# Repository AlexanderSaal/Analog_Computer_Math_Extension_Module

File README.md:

# Analog Computer: Math Extension Module

This repository provides a math extension module for analog computing applications. The module provides two absolute value functions, two square-root functions, and one logarithmic value function (base $10$ and $e$) of the input. Each output features an indicator LED that provides visual feedback proportional to the output value.

## Module Schematic

**<ins>Absolute function(x):</ins>** $x \rightarrow |x|$

The circuit for the absolute value function incorporates two different designs.

The left circuit is based on individual diodes and represents the classical implementation of an absolute value circuit. This circuit follows the design outlined in the document [PRECISION ABSOLUTE VALUE CIRCUITS](https://www.ti.com/lit/pdf/sboa068) from BURR-BROWN/TI.

The right circuit is similar but with one important difference: the diodes are replaced with P-channel MOSFETs on a single substrate. This should ensure thermal coupling and closely specifications of the two MOSFETs.

**<ins>Square-Root function(x):</ins>** $x \rightarrow \sqrt{x}$

The circuit implementation of the square-root function is based on the feedback principle. A multiplier squares the output signal and feeds it back into an open-loop amplifier to yield the inverse function. The diode in the feedback path ensures that only negative values are allowed at the input; otherwise, the output remains close to zero, preventing overload. For ease of use, an inverter is placed before the input, resulting in the overall transfer function of the module:

$$
\begin{align}
  f(x) = \begin{cases}
  \sqrt{x} & \text{if } x > 0 \\
  0 & \text{if } x \le 0
  \end{cases}
\end{align}
$$

This circuit design is based on the schematic and principals presented in the book [Analog and Hybrid Computer Programming](https://www.degruyter.com/document/doi/10.1515/9783110662207/html) by Prof. Dr. Bernd Ulmann and the [book on the THAT Analog Computer](http://www.astro-electronic.de/THAT_Analog_Computer_Book.pdf) by Michael Koch.

**<ins>Logarithmic function(x):</ins>** $x \rightarrow \mathrm{log}_{10}(x)$ and $x \rightarrow \mathrm{log}_{e}(x)$

The logarithm function circuit is based on the [LOG200](https://www.ti.com/product/LOG200) chip from Texas Instruments. The input voltage must be scaled down from $\pm 10 \, V$ to the chip's maximum accepted range of $\pm 5 \, V$. According to the datasheet, $-5V$ falls within the absolute maximum ratings and will not damage the chip.

The transfer function of the LOG200 chip is

$$ V_\mathrm{LOG} = 250 \, mV \cdot \mathrm{log}_{10} \left( \frac{I_1}{I_2} \right) $$

which depends on the ratio of the input currents $I_1$ and $I_2$. The input current $I_2$ is wired to the internal $1 \, \mu A$ precision current source. Accordingly, the input voltage has to be scaled using a precision (0.05\%) $50k\Omega$ resistor to give the appropriate current $I_1$. Since we want to map the output to the full range of our machine unit, $\pm1$ or $\pm 10 \,V$, a "20x" amplifier is placed after the output of the Voltage $V_\mathrm{LOG}$.

With this scaling, the following input-output relationship is achieved:

| Input      | Current $I_1$ | Output of LOG200 | Circuit Output |
|------------|---------------|------------------|----------------|
|$0.001 \, V$|$0.01 \, \mu A$|$-0.5\,V$         | $-10 \, V$     |
|$0.01 \, V$ |$0.1 \, \mu A$ |$-0.25\,V$        | $-5 \, V$      |
|$0.1 \, V$  |$1 \, \mu A$   |$0\,V$            | $0 \, V$       |
|$1 \, V$    |$10 \, \mu A$  |$0.25\,V$         | $5 \, V$       |
|$10 \, V$   |$100 \, \mu A$ |$0.5\,V$          | $10 \, V$      |

To additionally compute the natural logarithm $\mathrm{log}_e$, we use the relation:

$$ \mathrm{log}_{e}(x) = \frac{\mathrm{log}_{10}(x)}{\mathrm{log}_{10}(e)} = 2.303 \cdot \mathrm{log}_{10}(x) $$

A simple scaling amplifier with a gain of $0.2303x$ is used to provide the output of $\mathrm{log}_e(x) / 10$.

This circuit design and Input/Output scaling are based on the circuit presented in the book [Analog and Hybrid Computer Programming](https://www.degruyter.com/document/doi/10.1515/9783110662207/html) by Prof. Dr. Bernd Ulmann. I took the liberty of replacing the LOG112 with the LOG200 chip and adding the natural logarithm functionality.

## BOM

**<ins>Main Module:</ins>** 

|Reference                                   |Value              |Footprint                          |QUANTITY|
|--------------------------------------------|-------------------|-----------------------------------|--------|
|C1,C2,C14,C17                               |10u                |1206 / 3216Metric                  |4       |
|C3,C5                                       |0.33u              |1206 / 3216Metric                  |2       |
|C4,C6,C9,C10,C15,C16,C19,C20,C22-C25,C27,C28|1u                 |1206 / 3216Metric                  |14      |
|C7,C8                                       |10p                |1206 / 3216Metric                  |2       |
|C11,C12                                     |33p                |1206 / 3216Metric                  |2       |
|C13,C18                                     |1n                 |1206 / 3216Metric                  |2       |
|C21,C26                                     |68p                |1206 / 3216Metric                  |2       |
|D1                                          |12V_GREEN          |1206 / 3216Metric                  |1       |
|D2                                          |-12V_RED           |1206 / 3216Metric                  |1       |
|D3-D6                                       |BAT43W-V           |1206 / 3216Metric                  |4       |
|IC1,IC2                                     |AD633              |SOIC-8                             |2       |
|J1                                          |Conn_01x23_Pin     |PinHeader_1x23_P2.54mm_Vertical    |1       |
|J2                                          |Conn_02x05_Odd_Even|PinHeader_2x05_P2.54mm_Vertical    |1       |
|Q1                                          |PMV250EPEA         |SOT-23                             |1       |
|Q2                                          |PMV450ENEA         |SOT-23                             |1       |
|R1                                          |11k2               |1206 / 3216Metric                  |1       |
|R2                                          |5k6                |1206 / 3216Metric                  |1       |
|R3-R8,R14                                   |100k               |1206 / 3216Metric                  |7       |
|R9                                          |50k (0.05p)        |1206 / 3216Metric                  |1       |
|R10,R11                                     |1M (0.05p)         |1206 / 3216Metric                  |2       |
|R12,R29-R32                                 |3k9                |1206 / 3216Metric                  |5       |
|R13                                         |1M5                |1206 / 3216Metric                  |1       |
|R15                                         |4.26k              |1206 / 3216Metric                  |1       |
|R16                                         |400k               |1206 / 3216Metric                  |1       |
|R17,R18,R22-R24,R28                         |100k (0.1p)        |1206 / 3216Metric                  |6       |
|R19,R20,R25,R26                             |1M (0.1p)          |1206 / 3216Metric                  |4       |
|R21,R27                                     |25k (0.1p)         |1206 / 3216Metric                  |2       |
|RV1                                         |100k               |Potentiometer_Bourns_3296W_Vertical|1       |
|RV2                                         |2k                 |Potentiometer_Bourns_3296W_Vertical|1       |
|U1                                          |MC7805ACTG         |TO-220-3_Vertical                  |1       |
|U2                                          |MC7905BTG          |TO-220-3_Vertical                  |1       |
|U3,U4                                       |VCAN16A2           |VCAN16A2-03S-E3-08                 |2       |
|U5                                          |SI3993CDV-T1-GE3   |TSOT-23-6                          |1       |
|U6,U8-U10                                   |TLE2074IDWR        |SOIC-14\_3.9x8.7mm\_P1.27mm        |4       |
|U7                                          |LOG200             |VQFN-16                            |1       |

**<ins>Middleplate:</ins>**

|Reference                                   |Value              |Footprint                          |QUANTITY|
|--------------------------------------------|-------------------|-----------------------------------|--------|
|D1-D5                                       |BI color LED       |LED_D3.0mm_FlatTop                 |5       |
|J1                                          |Conn_01x23_Pin     |PinSocket_1x23_P2.54mm_Vertical    |1       |
|U1-U6                                       |VCAN16A2           |VCAN16A2-03S-E3-08                 |6       |

## List of special Components:

- OP-amp: [TLE2074IDWR](https://www.digikey.de/en/products/detail/texas-instruments/TLE2074IDWR/2799317) (Upgrade of the [TL074HIDR](https://www.digikey.de/en/products/detail/texas-instruments/TL074HIDR/13563033))
- logarithmic amplifier: [TL441CN](https://www.digikey.de/de/products/detail/texas-instruments/TL441CN/1675117), [LOG112AID](https://www.digikey.de/de/products/detail/texas-instruments/LOG112AID/486371), [LOG200RGTT](https://www.digikey.de/de/products/detail/texas-instruments/LOG200RGTT/25821029), [LOG200-datasheet](https://www.ti.com/product/LOG200)
- Multiplier: [AD633JRZ](https://www.digikey.de/en/products/detail/analog-devices-inc/AD633JRZ/617831) to [AD835ARZ](https://www.digikey.de/en/products/detail/analog-devices-inc/AD835ARZ-REEL7/621103)
- P-MOSFET: [SSFQ3805](https://www.digikey.de/en/products/detail/good-ark-semiconductor/SSFQ3805/18667583), [SI3993CDV-T1-GE3](https://www.digikey.de/en/products/detail/vishay-siliconix/SI3993CDV-T1-GE3/4876436)
- P-MOSFET (matched pair):[ALD1117SAL](https://www.digikey.de/en/products/detail/advanced-linear-devices-inc/ALD1117SAL/2414325)
- 16-BIT Schottky Barrier Diode Bus-Termination Array: [SN74S1053PWR](https://www.digikey.de/en/products/detail/texas-instruments/SN74S1053PWR/509741)
- 2 PNP (Dual) Matched Pair:[site](https://www.diodes.com/products/discrete-semiconductors/bipolar-transistors/transistor-bjt-master-table/matchedpair/#), [DMMT3906W-7-F](https://www.digikey.de/en/products/detail/diodes-incorporated/DMMT3906W-7-F/717760), [BCM847BS](https://www.digikey.de/en/products/detail/diotec-semiconductor/BCM847BS/22600802)
- +5V Regulator: [MC7805ACTG](https://www.digikey.de/en/products/detail/onsemi/MC7805ACTG/1481210), [MC7805ABTG](https://www.digikey.de/en/products/detail/onsemi/MC7805ABTG/921035)
- -5V Regulator: [MC7905BTG](https://www.digikey.de/en/products/detail/onsemi/MC7905BTG/1481513)

## License

This work is published under the [CERN Open Hardware Licence Version 2 - Strongly Reciprocal](LICENSE)

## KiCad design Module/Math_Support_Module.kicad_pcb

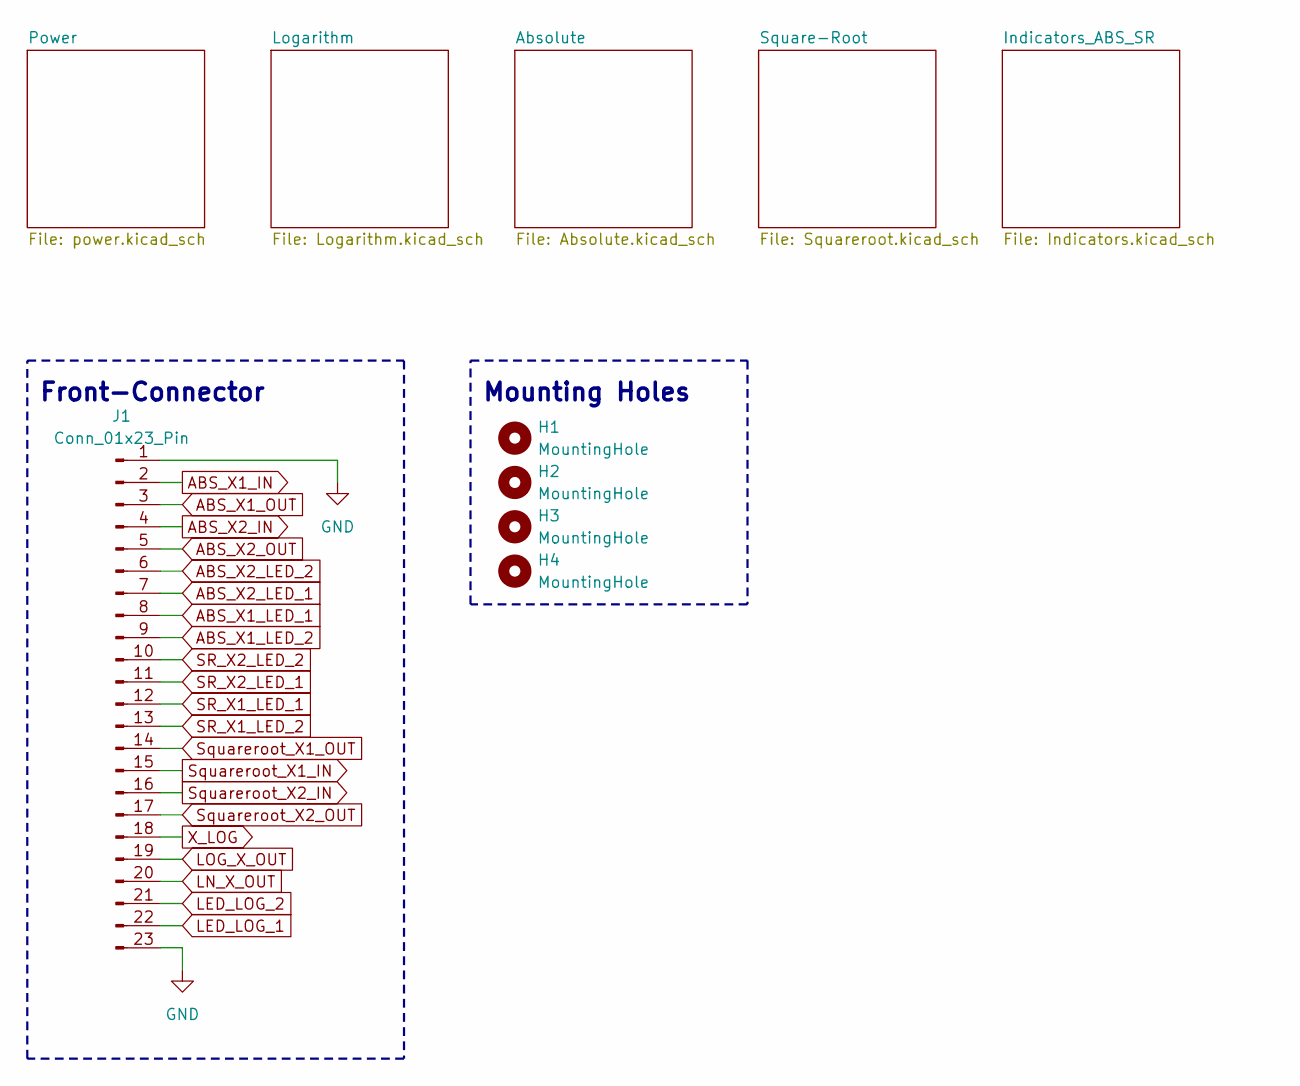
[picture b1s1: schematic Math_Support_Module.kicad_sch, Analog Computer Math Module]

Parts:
H1, H2, H3, H4: MountingHole; MountingHole_3.2mm_M3_DIN965
J1: Conn_01x23_Pin; PinHeader_1x23_P2.54mm_Vertical

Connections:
ABS_X1_IN: J1.2; also elsewhere on the board
ABS_X1_LED_1: J1.8; also elsewhere on the board
ABS_X1_LED_2: J1.9; also elsewhere on the board
ABS_X1_OUT: J1.3; also elsewhere on the board
ABS_X2_IN: J1.4; also elsewhere on the board
ABS_X2_LED_1: J1.7; also elsewhere on the board
ABS_X2_LED_2: J1.6; also elsewhere on the board
ABS_X2_OUT: J1.5; also elsewhere on the board
GND: J1.1, J1.23; also elsewhere on the board
LED_LOG_1: J1.22; also elsewhere on the board
LED_LOG_2: J1.21; also elsewhere on the board
LN_X_OUT: J1.20; also elsewhere on the board
LOG_X_OUT: J1.19; also elsewhere on the board
SR_X1_LED_1: J1.12; also elsewhere on the board
SR_X1_LED_2: J1.13; also elsewhere on the board
SR_X2_LED_1: J1.11; also elsewhere on the board
SR_X2_LED_2: J1.10; also elsewhere on the board
Squareroot_X1_IN: J1.15; also elsewhere on the board
Squareroot_X1_OUT: J1.14; also elsewhere on the board
Squareroot_X2_IN: J1.16; also elsewhere on the board
Squareroot_X2_OUT: J1.17; also elsewhere on the board
X_LOG: J1.18; also elsewhere on the board

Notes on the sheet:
Mounting Holes
Front-Connector

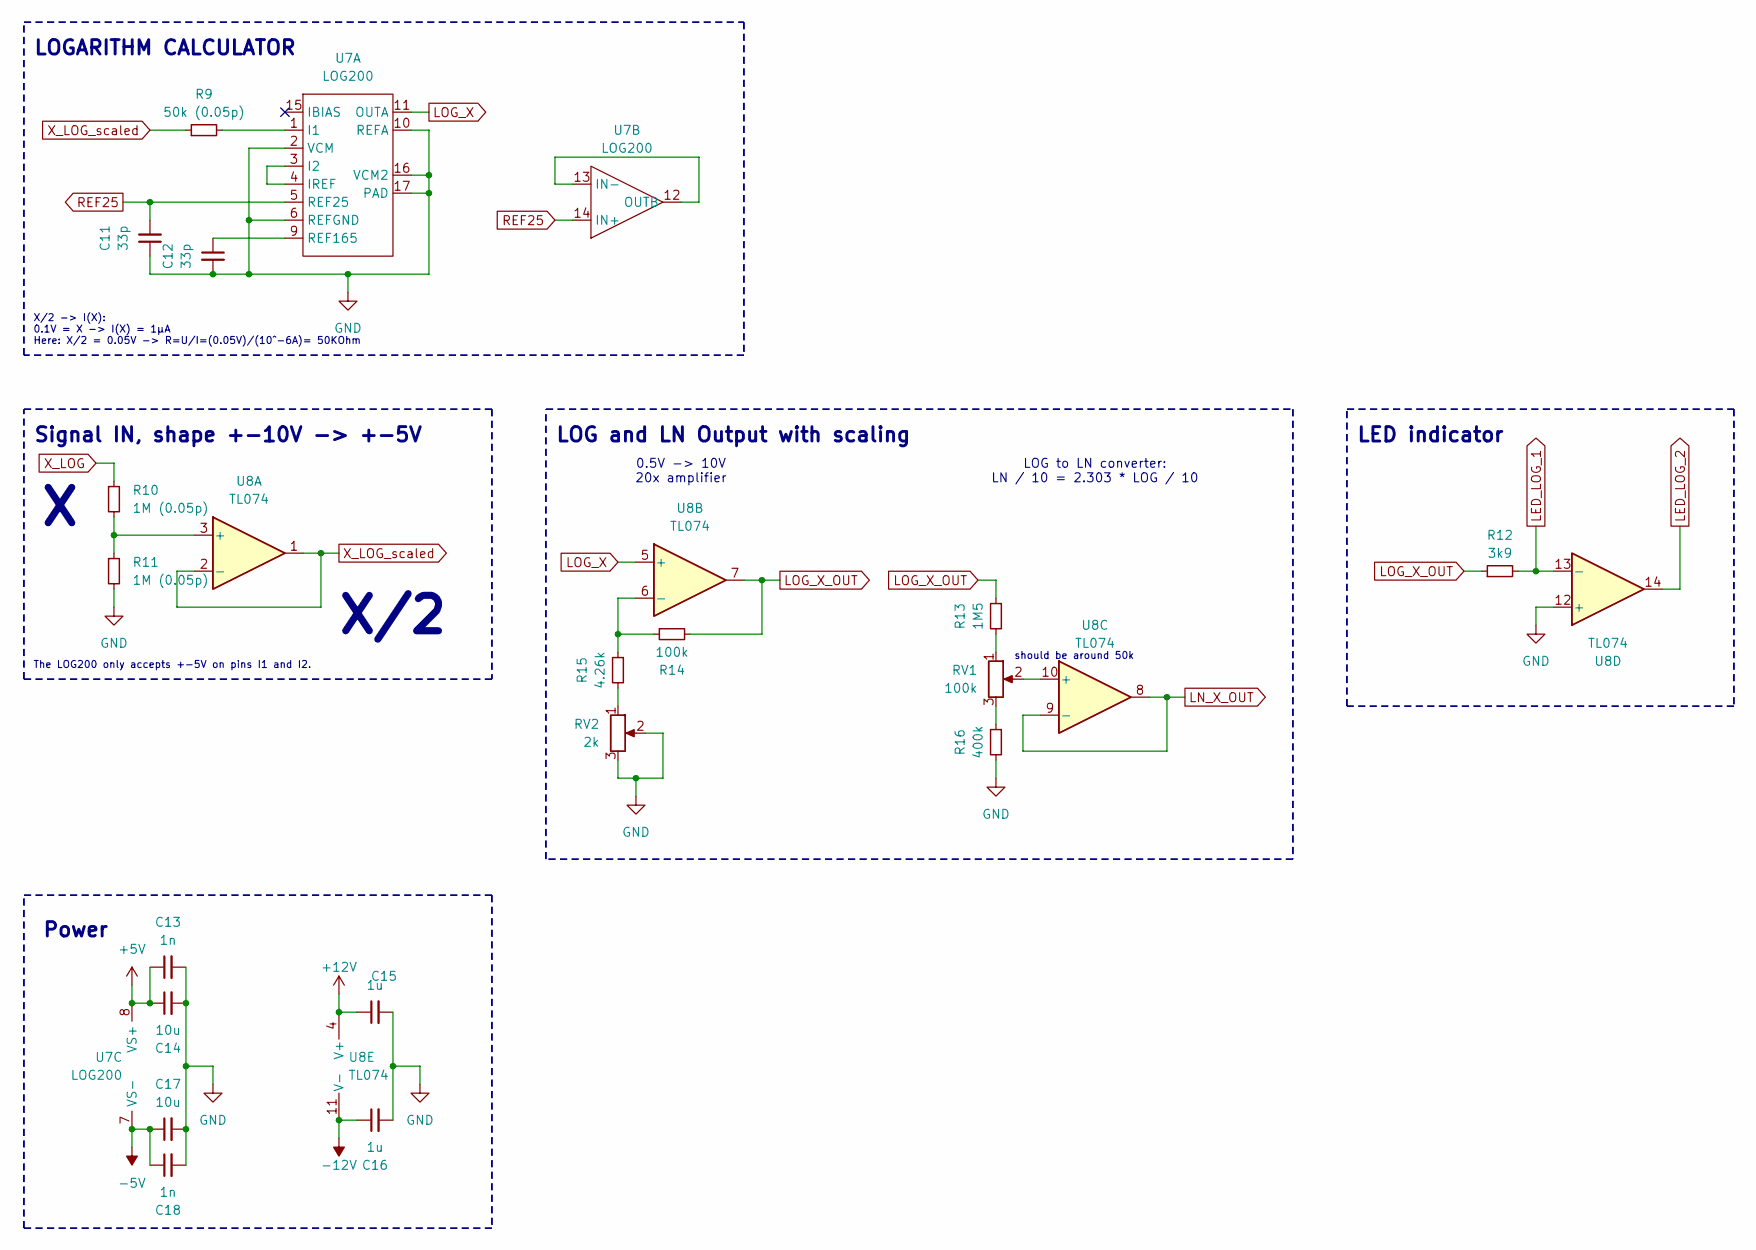
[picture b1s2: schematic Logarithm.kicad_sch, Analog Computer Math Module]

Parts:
C11, C12: 33p; C_1206_3216Metric_Pad1.33x1.80mm_HandSolder
C13, C18: 1n; C_1206_3216Metric_Pad1.33x1.80mm_HandSolder
C14, C17: 10u; C_1206_3216Metric_Pad1.33x1.80mm_HandSolder
C15, C16: 1u; C_1206_3216Metric_Pad1.33x1.80mm_HandSolder
R9: 50k (0.05p); R_1206_3216Metric_Pad1.30x1.75mm_HandSolder
R10, R11: 1M (0.05p); R_1206_3216Metric_Pad1.30x1.75mm_HandSolder
R12: 3k9; R_1206_3216Metric_Pad1.30x1.75mm_HandSolder
R13: 1M5; R_1206_3216Metric_Pad1.30x1.75mm_HandSolder
R14: 100k; R_1206_3216Metric_Pad1.30x1.75mm_HandSolder
R15: 4.26k; R_1206_3216Metric_Pad1.30x1.75mm_HandSolder
R16: 400k; R_1206_3216Metric_Pad1.30x1.75mm_HandSolder
RV1: 100k; Potentiometer_Bourns_3296W_Vertical
RV2: 2k; Potentiometer_Bourns_3296W_Vertical
U7: LOG200; VQFN-16-1EP_3x3mm_P0.5mm_EP1.6x1.6mm_ThermalVias
U8: TL074; SOIC-14_3.9x8.7mm_P1.27mm

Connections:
+5V: C13.1, C14.1, U7.8 (VS+); also elsewhere on the board
+12V: C15.1, U8.4 (V+); also elsewhere on the board
-5V: C17.1, C18.1, U7.7 (VS-); also elsewhere on the board
-12V: C16.1, U8.11 (V-); also elsewhere on the board
GND: C11.1, C12.2, C13.2, C14.2, C15.2, C16.2, C17.2, C18.2, R11.2, R16.2, RV2.2, RV2.3, U7.2 (VCM), U7.6 (REFGND), U7.10 (REFA), U7.16 (VCM2), U7.17 (PAD), U8.12 (+); also elsewhere on the board
LED_LOG_1: R12.2, U8.13 (-); also elsewhere on the board
LED_LOG_2: U8.14; also elsewhere on the board
LN_X_OUT: U8.8, U8.9 (-); also elsewhere on the board
LOG_X: U7.11 (OUTA), U8.5 (+)
LOG_X_OUT: R12.1, R13.1, R14.2, U8.7; also elsewhere on the board
unnamed: R13.2, RV1.1
unnamed: R15.2, RV2.1
unnamed: R16.1, RV1.3
unnamed: R9.2, U7.1 (I1)
unnamed: U7.3 (I2), U7.4 (IREF)
unnamed: C12.1, U7.9 (REF165)
unnamed: U7.12 (OUTB), U7.13 (IN-)
unnamed: R10.2, R11.1, U8.3 (+)
unnamed: R14.1, R15.1, U8.6 (-)
unnamed: RV1.2, U8.10 (+)
REF25: C11.2, U7.5 (REF25), U7.14 (IN+)
X_LOG: R10.1; also elsewhere on the board
X_LOG_scaled: R9.1, U8.1, U8.2 (-)

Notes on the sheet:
Power
X/2 -> I(X): 0.1V = X -> I(X) = 1µA Here: X/2 = 0.05V -> R=U/I=(0.05V)/(10^-6A)= 50KOhm
LED indicator
Signal IN, shape +-10V -> +-5V
LOG to LN converter: LN / 10 = 2.303 * LOG / 10
The LOG200 only accepts +-5V on pins I1 and I2.
X/2
0.5V -> 10V 20x amplifier
should be around 50k
LOGARITHM CALCULATOR
LOG and LN Output with scaling

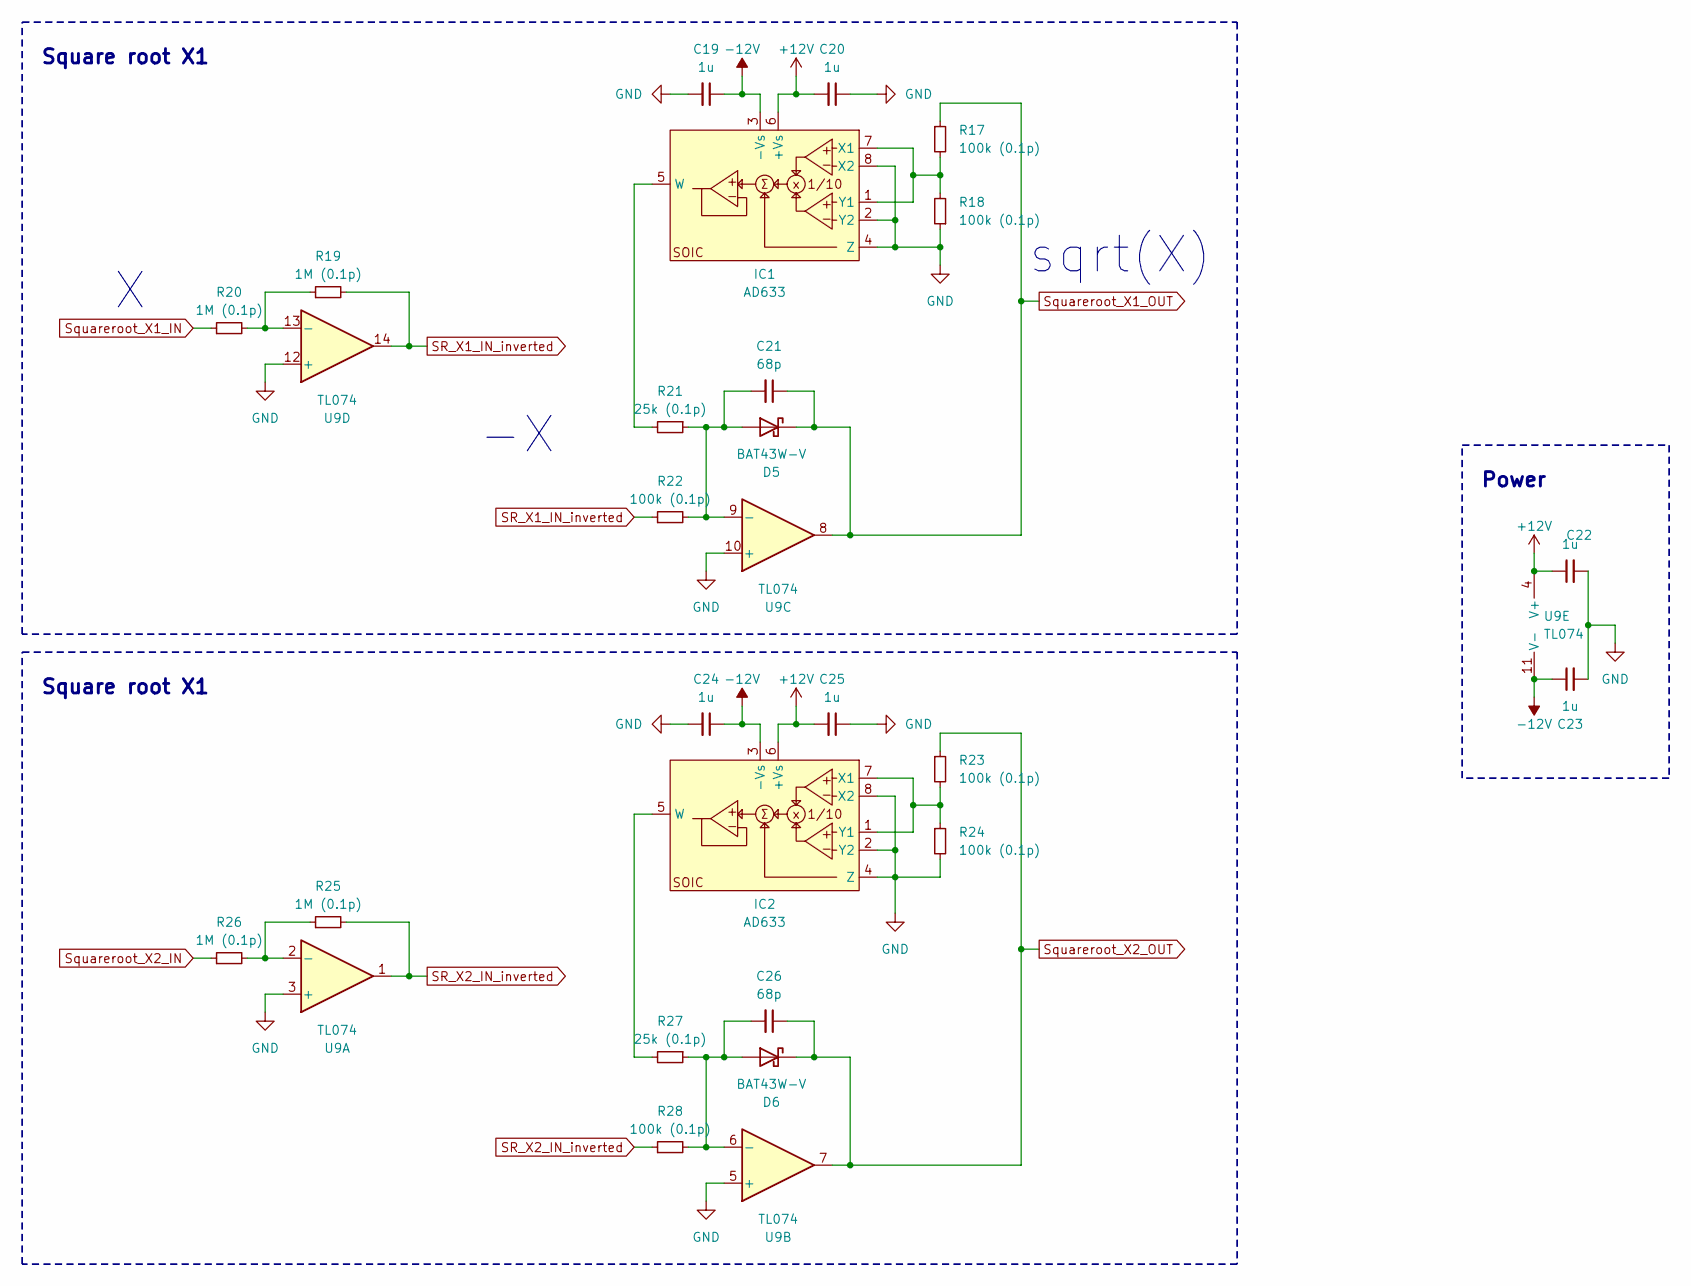
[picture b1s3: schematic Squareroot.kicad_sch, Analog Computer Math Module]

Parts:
C19, C20, C22, C23, C24, C25: 1u; C_1206_3216Metric_Pad1.33x1.80mm_HandSolder
C21, C26: 68p; C_1206_3216Metric_Pad1.33x1.80mm_HandSolder
D5, D6: BAT43W-V; D_1206_3216Metric_Pad1.42x1.75mm_HandSolder
IC1, IC2: AD633; SOIC-8_3.9x4.9mm_P1.27mm
R17, R18, R22, R23, R24, R28: 100k (0.1p); R_1206_3216Metric_Pad1.30x1.75mm_HandSolder
R19, R20, R25, R26: 1M (0.1p); R_1206_3216Metric_Pad1.30x1.75mm_HandSolder
R21, R27: 25k (0.1p); R_1206_3216Metric_Pad1.30x1.75mm_HandSolder
U9: TL074; SOIC-14_3.9x8.7mm_P1.27mm

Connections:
+12V: C20.2, C22.1, C25.2, IC1.6 (+Vs), IC2.6 (+Vs), U9.4 (V+); also elsewhere on the board
-12V: C19.1, C23.1, C24.1, IC1.3 (-Vs), IC2.3 (-Vs), U9.11 (V-); also elsewhere on the board
GND: C19.2, C20.1, C22.2, C23.2, C24.2, C25.1, IC1.2 (Y2), IC1.4 (Z), IC1.8 (X2), IC2.2 (Y2), IC2.4 (Z), IC2.8 (X2), R18.1, R24.2, U9.3 (+), U9.5 (+), U9.10 (+), U9.12 (+); also elsewhere on the board
unnamed: C21.2, D5.2 (A), R21.1, R22.2, U9.9 (-)
unnamed: C26.2, D6.2 (A), R27.1, R28.2, U9.6 (-)
unnamed: IC1.5 (W), R21.2
unnamed: IC1.1 (Y1), IC1.7 (X1), R17.2, R18.2
unnamed: IC2.5 (W), R27.2
unnamed: IC2.1 (Y1), IC2.7 (X1), R23.2, R24.1
unnamed: R25.1, R26.2, U9.2 (-)
unnamed: R19.1, R20.2, U9.13 (-)
SR_X1_IN_inverted: R19.2, R22.1, U9.14
SR_X2_IN_inverted: R25.2, R28.1, U9.1
Squareroot_X1_IN: R20.1; also elsewhere on the board
Squareroot_X1_OUT: C21.1, D5.1 (K), R17.1, U9.8; also elsewhere on the board
Squareroot_X2_IN: R26.1; also elsewhere on the board
Squareroot_X2_OUT: C26.1, D6.1 (K), R23.1, U9.7; also elsewhere on the board

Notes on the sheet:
sqrt(X)
Power
Square root X1

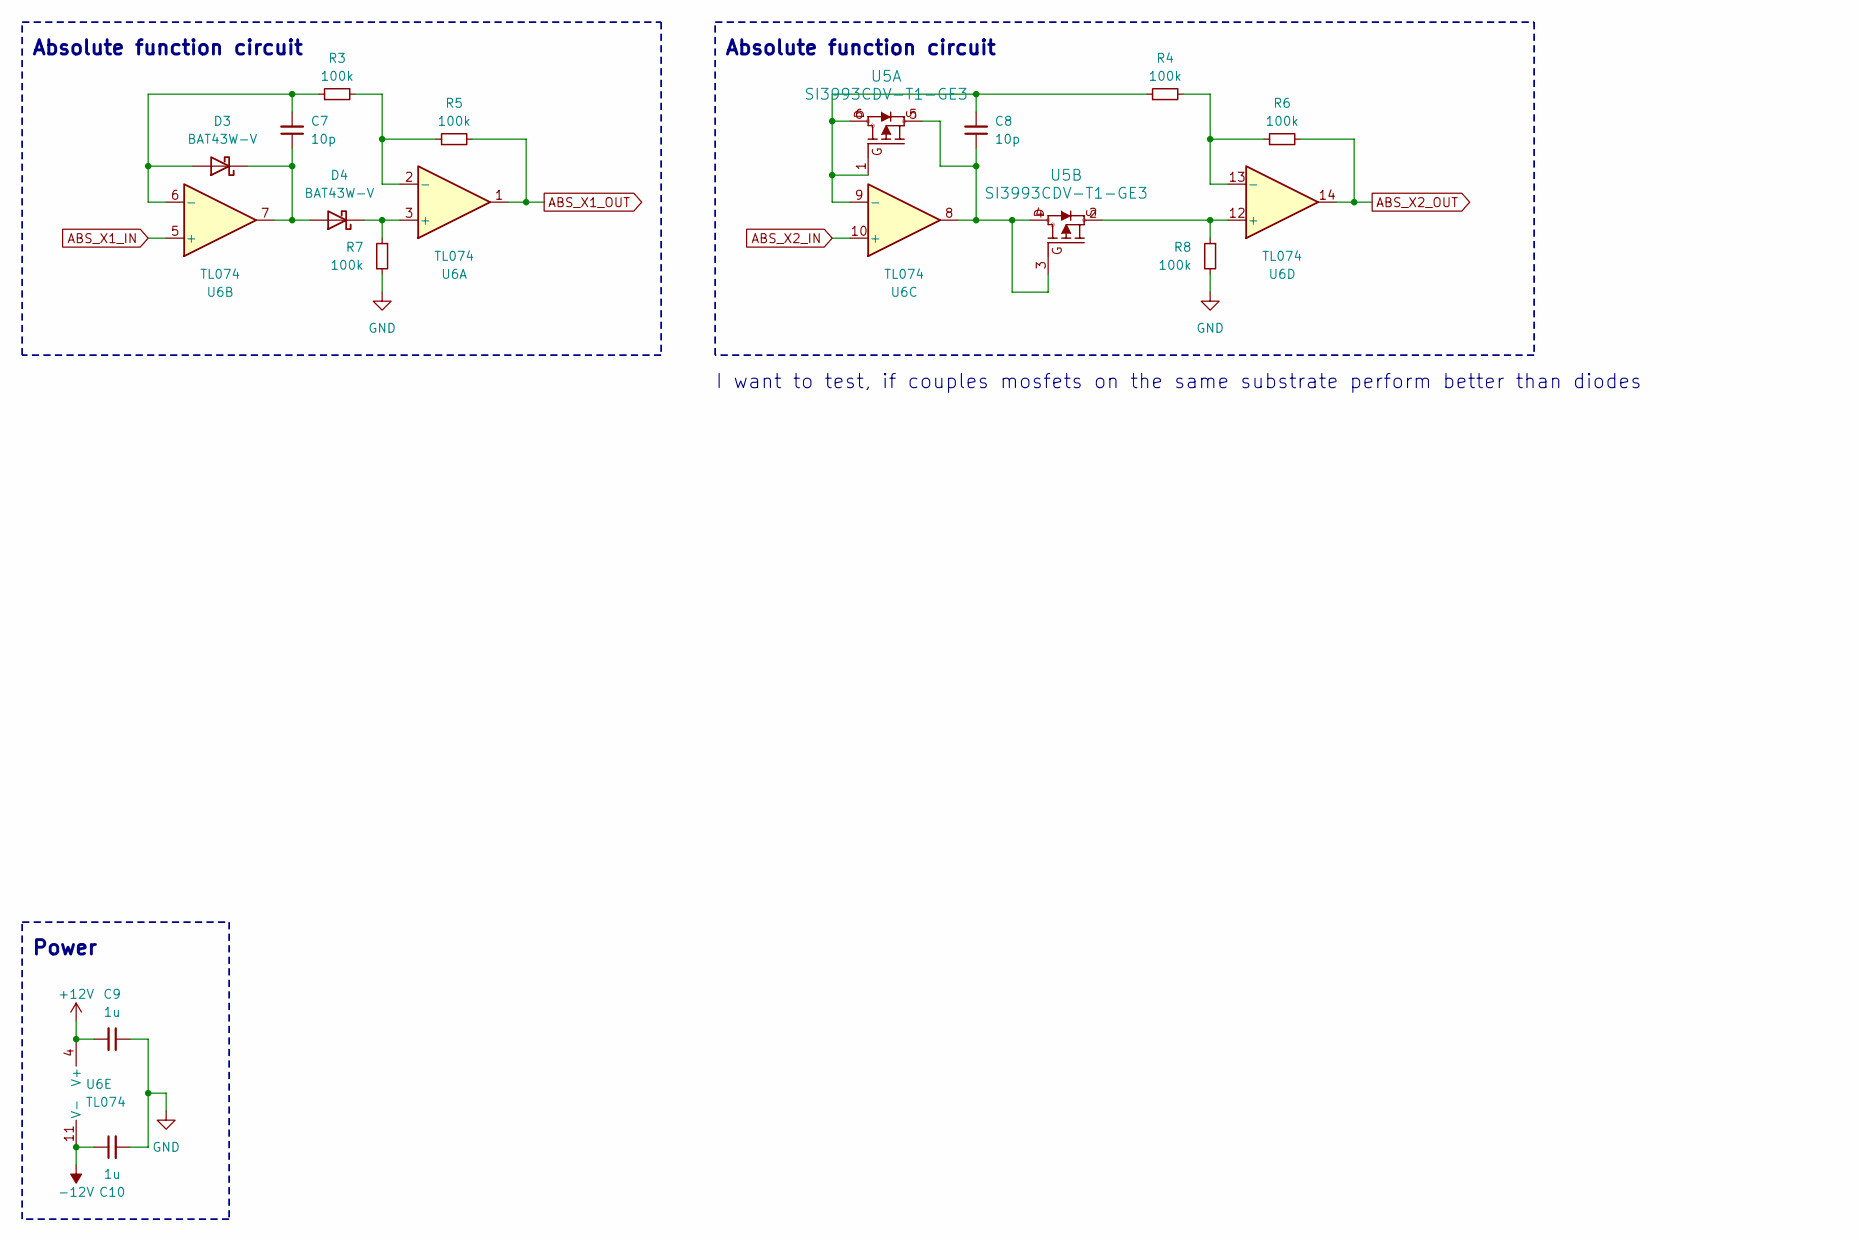
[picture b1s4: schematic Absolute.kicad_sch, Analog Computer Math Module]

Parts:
C7, C8: 10p; C_1206_3216Metric_Pad1.33x1.80mm_HandSolder
C9, C10: 1u; C_1206_3216Metric_Pad1.33x1.80mm_HandSolder
D3, D4: BAT43W-V; D_1206_3216Metric_Pad1.42x1.75mm_HandSolder
R3, R4, R5, R6, R7, R8: 100k; R_1206_3216Metric_Pad1.30x1.75mm_HandSolder
U5: SI3993CDV-T1-GE3; TSOT-23-6_HandSoldering
U6: TL074; SOIC-14_3.9x8.7mm_P1.27mm

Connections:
+12V: C9.2, U6.4 (V+); also elsewhere on the board
-12V: C10.1, U6.11 (V-); also elsewhere on the board
ABS_X1_IN: U6.5 (+); also elsewhere on the board
ABS_X1_OUT: R5.2, U6.1; also elsewhere on the board
ABS_X2_IN: U6.10 (+); also elsewhere on the board
ABS_X2_OUT: R6.2, U6.14; also elsewhere on the board
GND: C9.1, C10.2, R7.2, R8.2; also elsewhere on the board
unnamed: C7.2, D3.2 (A), R3.1, U6.6 (-)
unnamed: C7.1, D3.1 (K), D4.2 (A), U6.7
unnamed: D4.1 (K), R7.1, U6.3 (+)
unnamed: C8.2, R4.1, U5.1 (G1), U5.6 (D1), U6.9 (-)
unnamed: C8.1, U5.3 (G2), U5.4 (D2), U5.5 (S1), U6.8
unnamed: R8.1, U5.2 (S2), U6.12 (+)
unnamed: R3.2, R5.1, U6.2 (-)
unnamed: R4.2, R6.1, U6.13 (-)

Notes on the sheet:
Absolute function circuit
Power
I want to test, if couples mosfets on the same substrate perform better than diodes

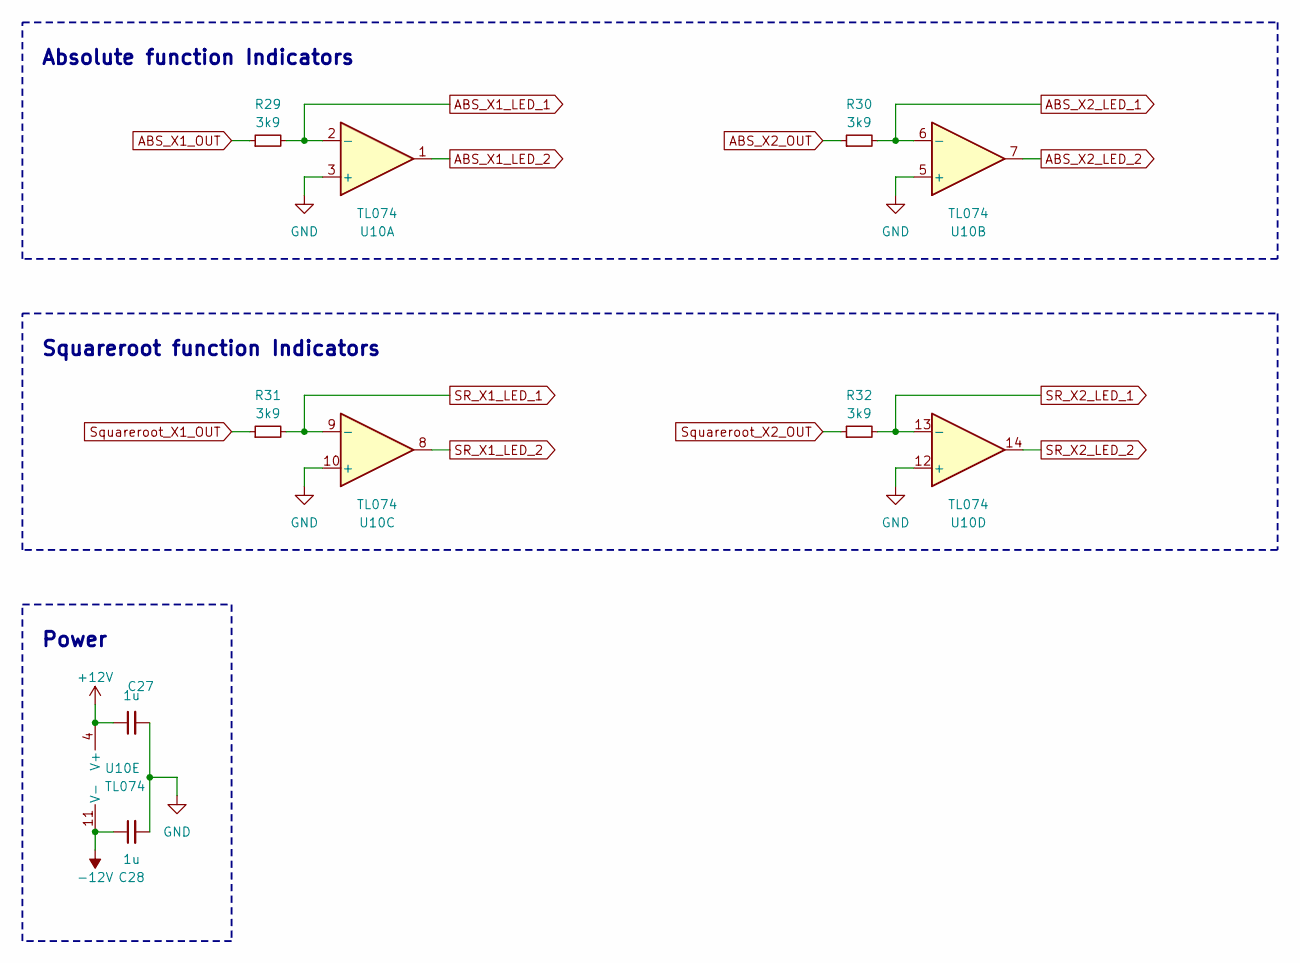
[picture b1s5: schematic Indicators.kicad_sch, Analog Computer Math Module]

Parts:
C27, C28: 1u; C_1206_3216Metric_Pad1.33x1.80mm_HandSolder
R29, R30, R31, R32: 3k9; R_1206_3216Metric_Pad1.30x1.75mm_HandSolder
U10: TL074; SOIC-14_3.9x8.7mm_P1.27mm

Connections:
+12V: C27.1, U10.4 (V+); also elsewhere on the board
-12V: C28.1, U10.11 (V-); also elsewhere on the board
ABS_X1_LED_1: R29.2, U10.2 (-); also elsewhere on the board
ABS_X1_LED_2: U10.1; also elsewhere on the board
ABS_X1_OUT: R29.1; also elsewhere on the board
ABS_X2_LED_1: R30.2, U10.6 (-); also elsewhere on the board
ABS_X2_LED_2: U10.7; also elsewhere on the board
ABS_X2_OUT: R30.1; also elsewhere on the board
GND: C27.2, C28.2, U10.3 (+), U10.5 (+), U10.10 (+), U10.12 (+); also elsewhere on the board
SR_X1_LED_1: R31.2, U10.9 (-); also elsewhere on the board
SR_X1_LED_2: U10.8; also elsewhere on the board
SR_X2_LED_1: R32.2, U10.13 (-); also elsewhere on the board
SR_X2_LED_2: U10.14; also elsewhere on the board
Squareroot_X1_OUT: R31.1; also elsewhere on the board
Squareroot_X2_OUT: R32.1; also elsewhere on the board

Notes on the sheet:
Squareroot function Indicators
Absolute function Indicators
Power

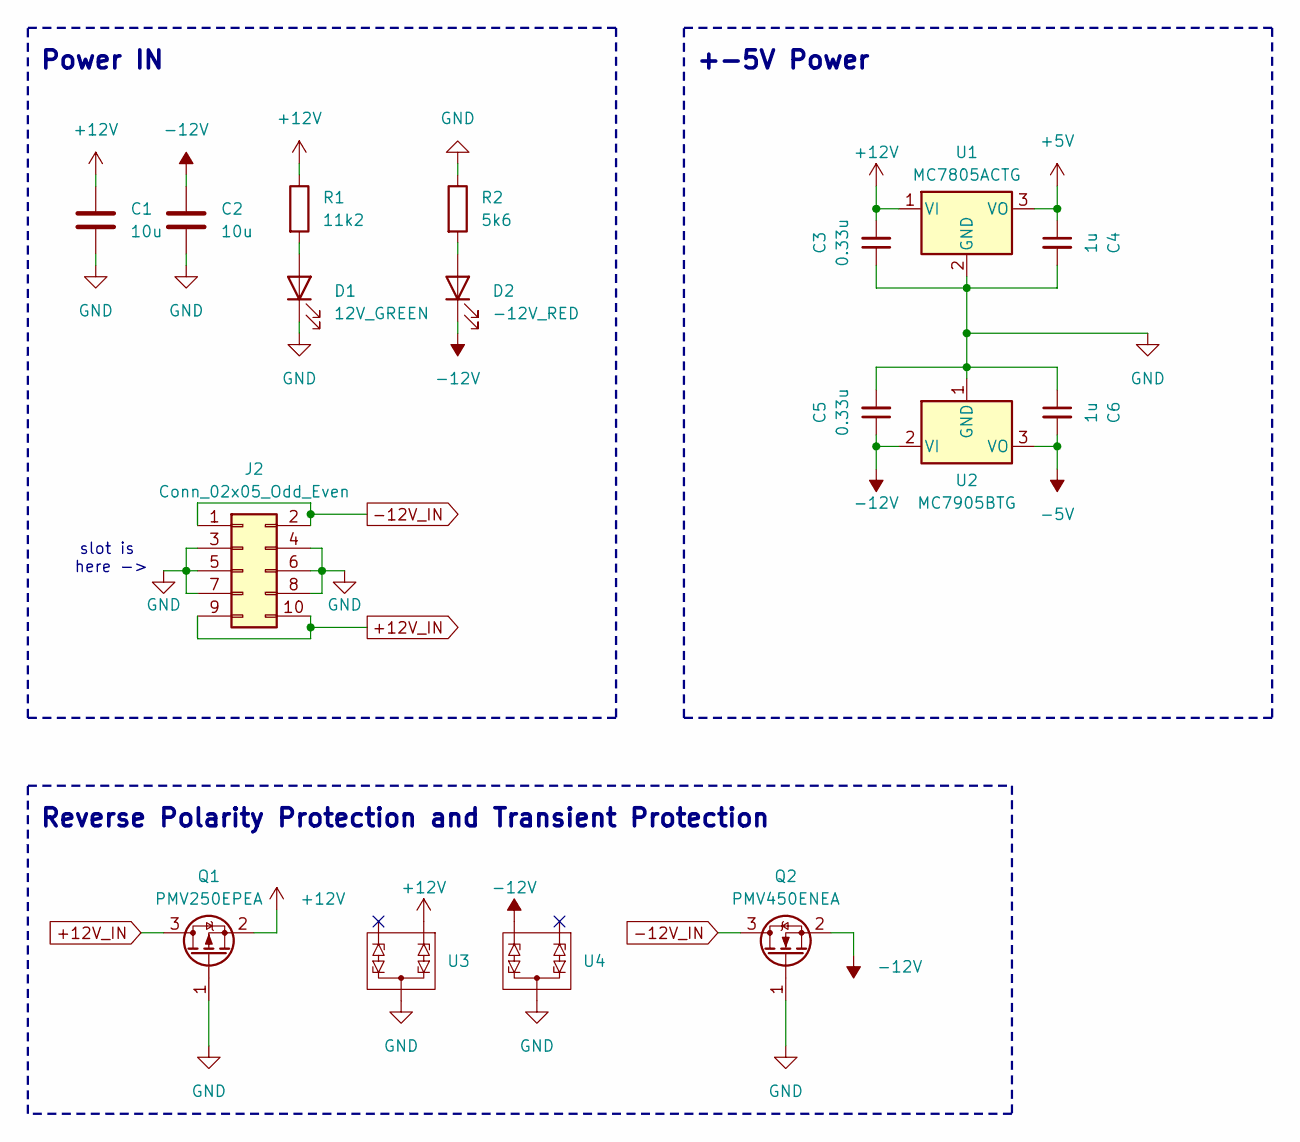
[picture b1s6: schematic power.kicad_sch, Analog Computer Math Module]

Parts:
C1, C2: 10u; C_1206_3216Metric_Pad1.33x1.80mm_HandSolder
C3, C5: 0.33u; C_1206_3216Metric_Pad1.33x1.80mm_HandSolder
C4, C6: 1u; C_1206_3216Metric_Pad1.33x1.80mm_HandSolder
D1: 12V_GREEN; LED_1206_3216Metric
D2: -12V_RED; LED_1206_3216Metric
J2: Conn_02x05_Odd_Even; PinHeader_2x05_P2.54mm_Vertical
Q1: PMV250EPEA; SOT-23_Handsoldering
Q2: PMV450ENEA; SOT-23_Handsoldering
R1: 11k2; R_1206_3216Metric_Pad1.30x1.75mm_HandSolder
R2: 5k6; R_1206_3216Metric_Pad1.30x1.75mm_HandSolder
U1: MC7805ACTG; TO-220-3_Vertical
U2: MC7905BTG; TO-220-3_Vertical
U3, U4: VCAN16A2; VCAN16A2-03S-E3-08

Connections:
+5V: C4.1, U1.3 (VO); also elsewhere on the board
+12V: C1.1, C3.2, Q1.2 (S), R1.1, U1.1 (VI), U3.1 (IN1); also elsewhere on the board
+12V_IN: J2.9, J2.10, Q1.3 (D)
-5V: C6.2, U2.3 (VO); also elsewhere on the board
-12V: C2.1, C5.1, D2.1 (K), Q2.2 (S), U2.2 (VI), U4.2 (IN2); also elsewhere on the board
-12V_IN: J2.1, J2.2, Q2.3 (D)
GND: C1.2, C2.2, C3.1, C4.2, C5.2, C6.1, D1.1 (K), J2.3, J2.4, J2.5, J2.6, J2.7, J2.8, Q1.1 (G), Q2.1 (G), R2.1, U1.2 (GND), U2.1 (GND), U3.3 (OUT), U4.3 (OUT); also elsewhere on the board
unnamed: D1.2 (A), R1.2
unnamed: D2.2 (A), R2.2

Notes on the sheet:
Reverse Polarity Protection and Transient Protection
Power IN
slot is here ->
+-5V Power

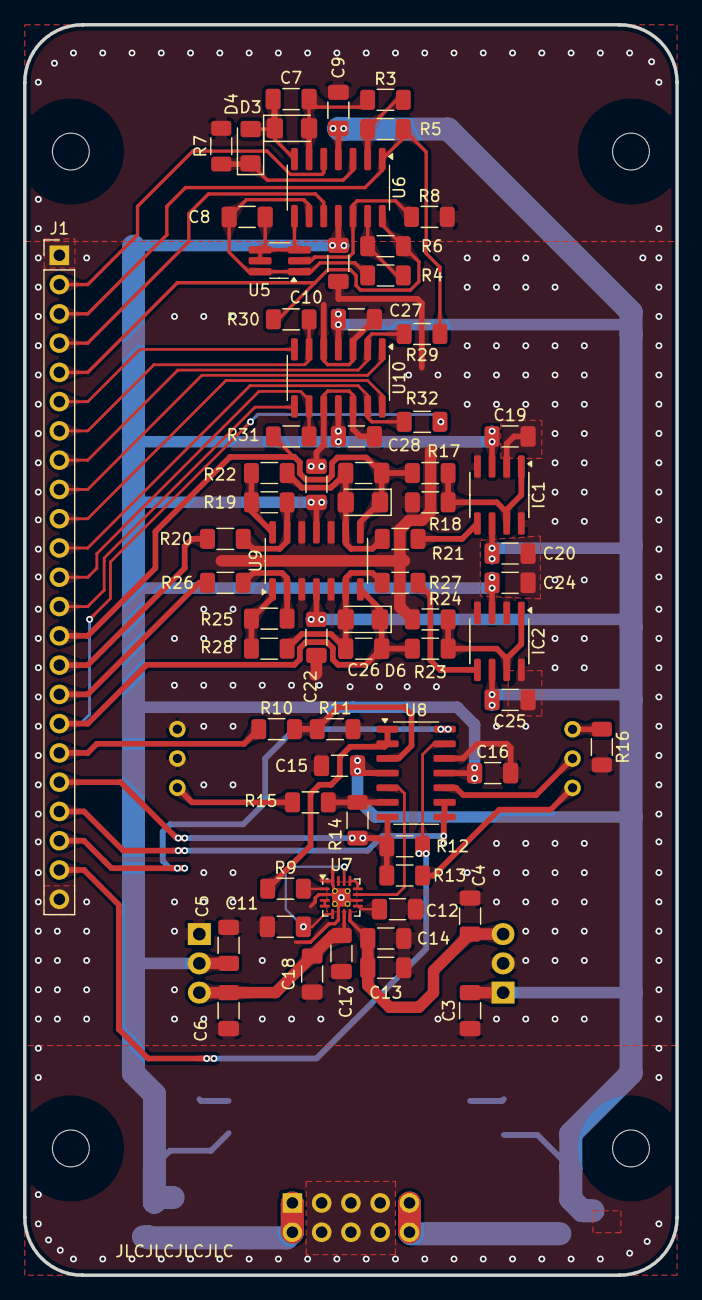
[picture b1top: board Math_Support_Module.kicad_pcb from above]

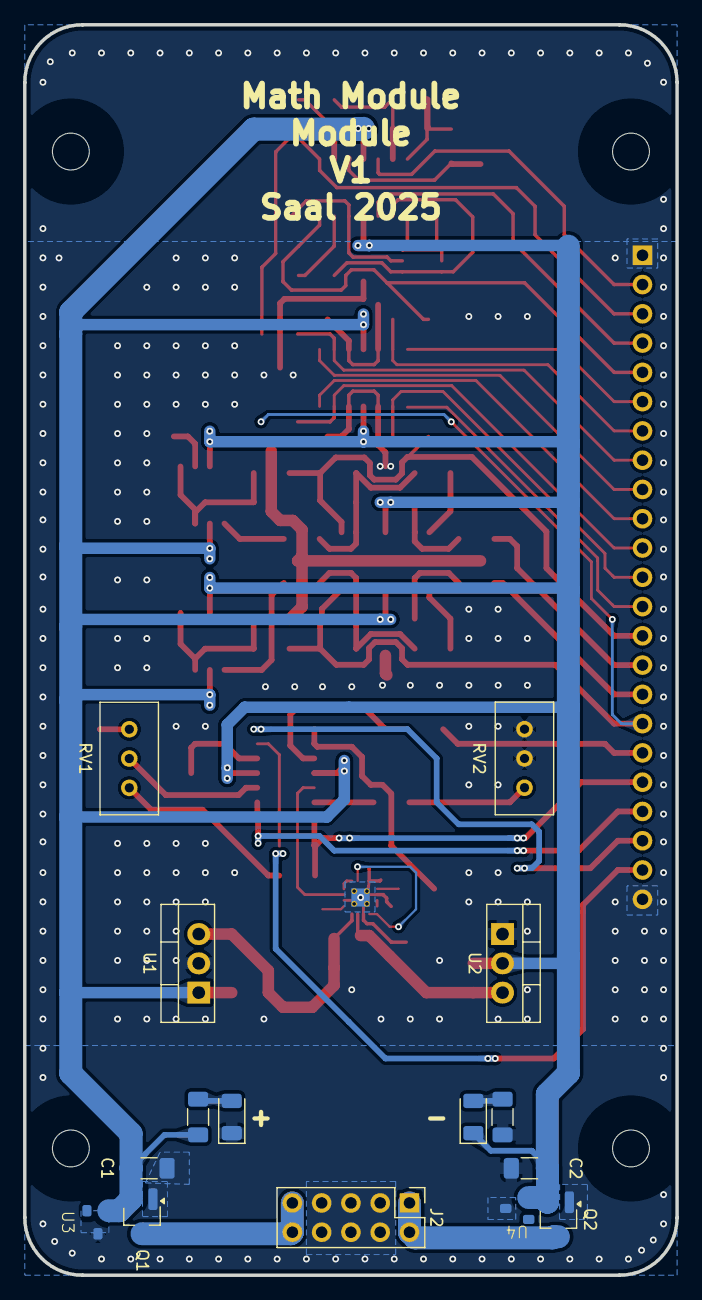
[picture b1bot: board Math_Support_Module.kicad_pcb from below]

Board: 2 copper layers, 56.6 x 108.5 mm, 88 parts (15 on the bottom side), 61 nets.

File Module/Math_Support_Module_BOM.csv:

"Reference","Value","Footprint","QUANTITY"
"C1,C2,C14,C17","10u","Capacitor_SMD:C_1206_3216Metric_Pad1.33x1.80mm_HandSolder","4"
"C3,C5","0.33u","Capacitor_SMD:C_1206_3216Metric_Pad1.33x1.80mm_HandSolder","2"
"C4,C6,C9,C10,C15,C16,C19,C20,C22-C25,C27,C28","1u","Capacitor_SMD:C_1206_3216Metric_Pad1.33x1.80mm_HandSolder","14"
"C7,C8","10p","Capacitor_SMD:C_1206_3216Metric_Pad1.33x1.80mm_HandSolder","2"
"C11,C12","33p","Capacitor_SMD:C_1206_3216Metric_Pad1.33x1.80mm_HandSolder","2"
"C13,C18","1n","Capacitor_SMD:C_1206_3216Metric_Pad1.33x1.80mm_HandSolder","2"
"C21,C26","68p","Capacitor_SMD:C_1206_3216Metric_Pad1.33x1.80mm_HandSolder","2"
"D1","12V_GREEN","LED_SMD:LED_1206_3216Metric","1"
"D2","-12V_RED","LED_SMD:LED_1206_3216Metric","1"
"D3-D6","BAT43W-V","Diode_SMD:D_1206_3216Metric_Pad1.42x1.75mm_HandSolder","4"
"IC1,IC2","AD633","Package_SO:SOIC-8_3.9x4.9mm_P1.27mm","2"
"J1","Conn_01x23_Pin","Connector_PinHeader_2.54mm:PinHeader_1x23_P2.54mm_Vertical","1"
"J2","Conn_02x05_Odd_Even","Connector_PinHeader_2.54mm:PinHeader_2x05_P2.54mm_Vertical","1"
"Q1","PMV250EPEA","Package_TO_SOT_SMD:SOT-23_Handsoldering","1"
"Q2","PMV450ENEA","Package_TO_SOT_SMD:SOT-23_Handsoldering","1"
"R1","11k2","Resistor_SMD:R_1206_3216Metric_Pad1.30x1.75mm_HandSolder","1"
"R2","5k6","Resistor_SMD:R_1206_3216Metric_Pad1.30x1.75mm_HandSolder","1"
"R3-R8,R14","100k","Resistor_SMD:R_1206_3216Metric_Pad1.30x1.75mm_HandSolder","7"
"R9","50k (0.05p)","Resistor_SMD:R_1206_3216Metric_Pad1.30x1.75mm_HandSolder","1"
"R10,R11","1M (0.05p)","Resistor_SMD:R_1206_3216Metric_Pad1.30x1.75mm_HandSolder","2"
"R12,R29-R32","3k9","Resistor_SMD:R_1206_3216Metric_Pad1.30x1.75mm_HandSolder","5"
"R13","1M5","Resistor_SMD:R_1206_3216Metric_Pad1.30x1.75mm_HandSolder","1"
"R15","4.26k","Resistor_SMD:R_1206_3216Metric_Pad1.30x1.75mm_HandSolder","1"
"R16","400k","Resistor_SMD:R_1206_3216Metric_Pad1.30x1.75mm_HandSolder","1"
"R17,R18,R22-R24,R28","100k (0.1p)","Resistor_SMD:R_1206_3216Metric_Pad1.30x1.75mm_HandSolder","6"
"R19,R20,R25,R26","1M (0.1p)","Resistor_SMD:R_1206_3216Metric_Pad1.30x1.75mm_HandSolder","4"
"R21,R27","25k (0.1p)","Resistor_SMD:R_1206_3216Metric_Pad1.30x1.75mm_HandSolder","2"
"RV1","100k","Potentiometer_THT:Potentiometer_Bourns_3296W_Vertical","1"
"RV2","2k","Potentiometer_THT:Potentiometer_Bourns_3296W_Vertical","1"
"U1","MC7805ACTG","Package_TO_SOT_THT:TO-220-3_Vertical","1"
"U2","MC7905BTG","Package_TO_SOT_THT:TO-220-3_Vertical","1"
"U3,U4","VCAN16A2","analog_computing:VCAN16A2-03S-E3-08","2"
"U5","SI3993CDV-T1-GE3","Package_TO_SOT_SMD:TSOT-23-6_HandSoldering","1"
"U6,U8-U10","TL074","Package_SO:SOIC-14_3.9x8.7mm_P1.27mm","4"
"U7","LOG200","Package_DFN_QFN:VQFN-16-1EP_3x3mm_P0.5mm_EP1.6x1.6mm_ThermalVias","1"
